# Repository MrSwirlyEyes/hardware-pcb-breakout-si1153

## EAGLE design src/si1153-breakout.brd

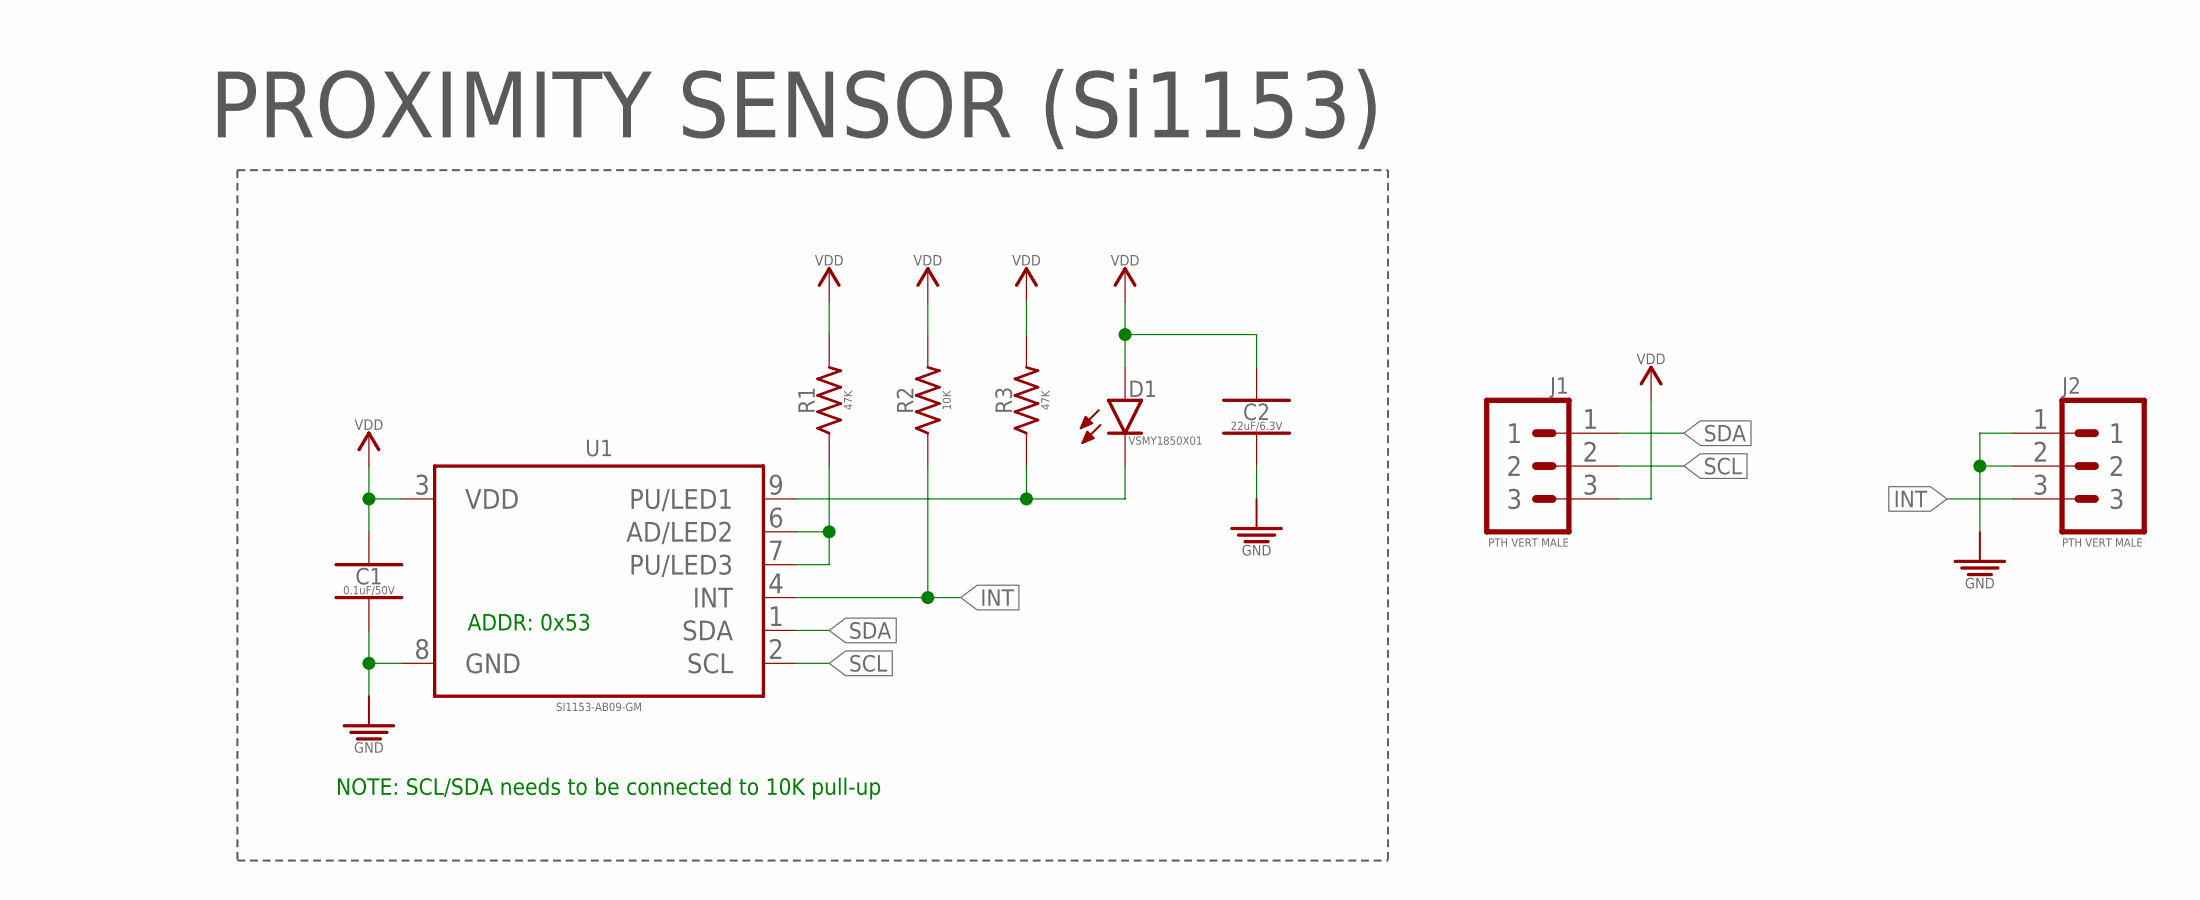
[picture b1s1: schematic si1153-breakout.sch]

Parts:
C1: 0.1uF/50V; CAPC1005X55_SMD-0402
C2: 22uF/6.3V; CAPC1005X55_SMD-0402
D1: VSMY1850X01; LEDC2012X120_LED-0805
J1, J2: PTH VERT MALE; HDRV3W64P254_1X3_762X254X838B
R1, R3: 47K; RESC1005X35_SMD-0402
R2: 10K; RESC1005X35_SMD-0402
U1: SI1153-AB09-GM; QFN50P200X200X75-10N

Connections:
GND: C1.2, C2.2, J2.1, J2.2, U1.8 (GND)
INT: J2.3, R2.1, U1.4 (INT)
unnamed: R1.1, U1.6 (AD/LED2), U1.7 (PU/LED3)
unnamed: D1.K, R3.1, U1.9 (PU/LED1)
SCL: J1.2, U1.2 (SCL)
SDA: J1.1, U1.1 (SDA)
VDD: C1.1, C2.1, D1.A, J1.3, R1.2, R2.2, R3.2, U1.3 (VDD)

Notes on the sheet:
PROXIMITY SENSOR (Si1153)
ADDR: 0x53
NOTE: SCL/SDA needs to be connected to 10K pull-up

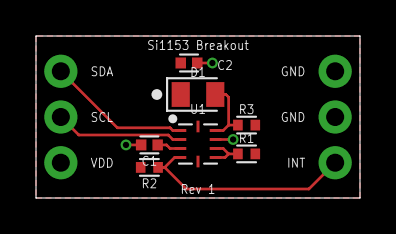
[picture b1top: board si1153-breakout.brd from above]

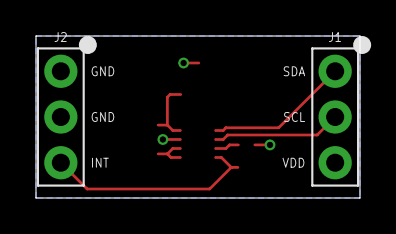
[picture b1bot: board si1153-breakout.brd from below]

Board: 2 copper layers, 18.0 x 9.0 mm, 9 parts (2 on the bottom side), 7 nets.

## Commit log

2021-01-12 [Rev 1] - Initialize repo.
2021-02-06 Update to fit OSH Park 2-layer DRU.
2021-08-11 Update CAM files.
